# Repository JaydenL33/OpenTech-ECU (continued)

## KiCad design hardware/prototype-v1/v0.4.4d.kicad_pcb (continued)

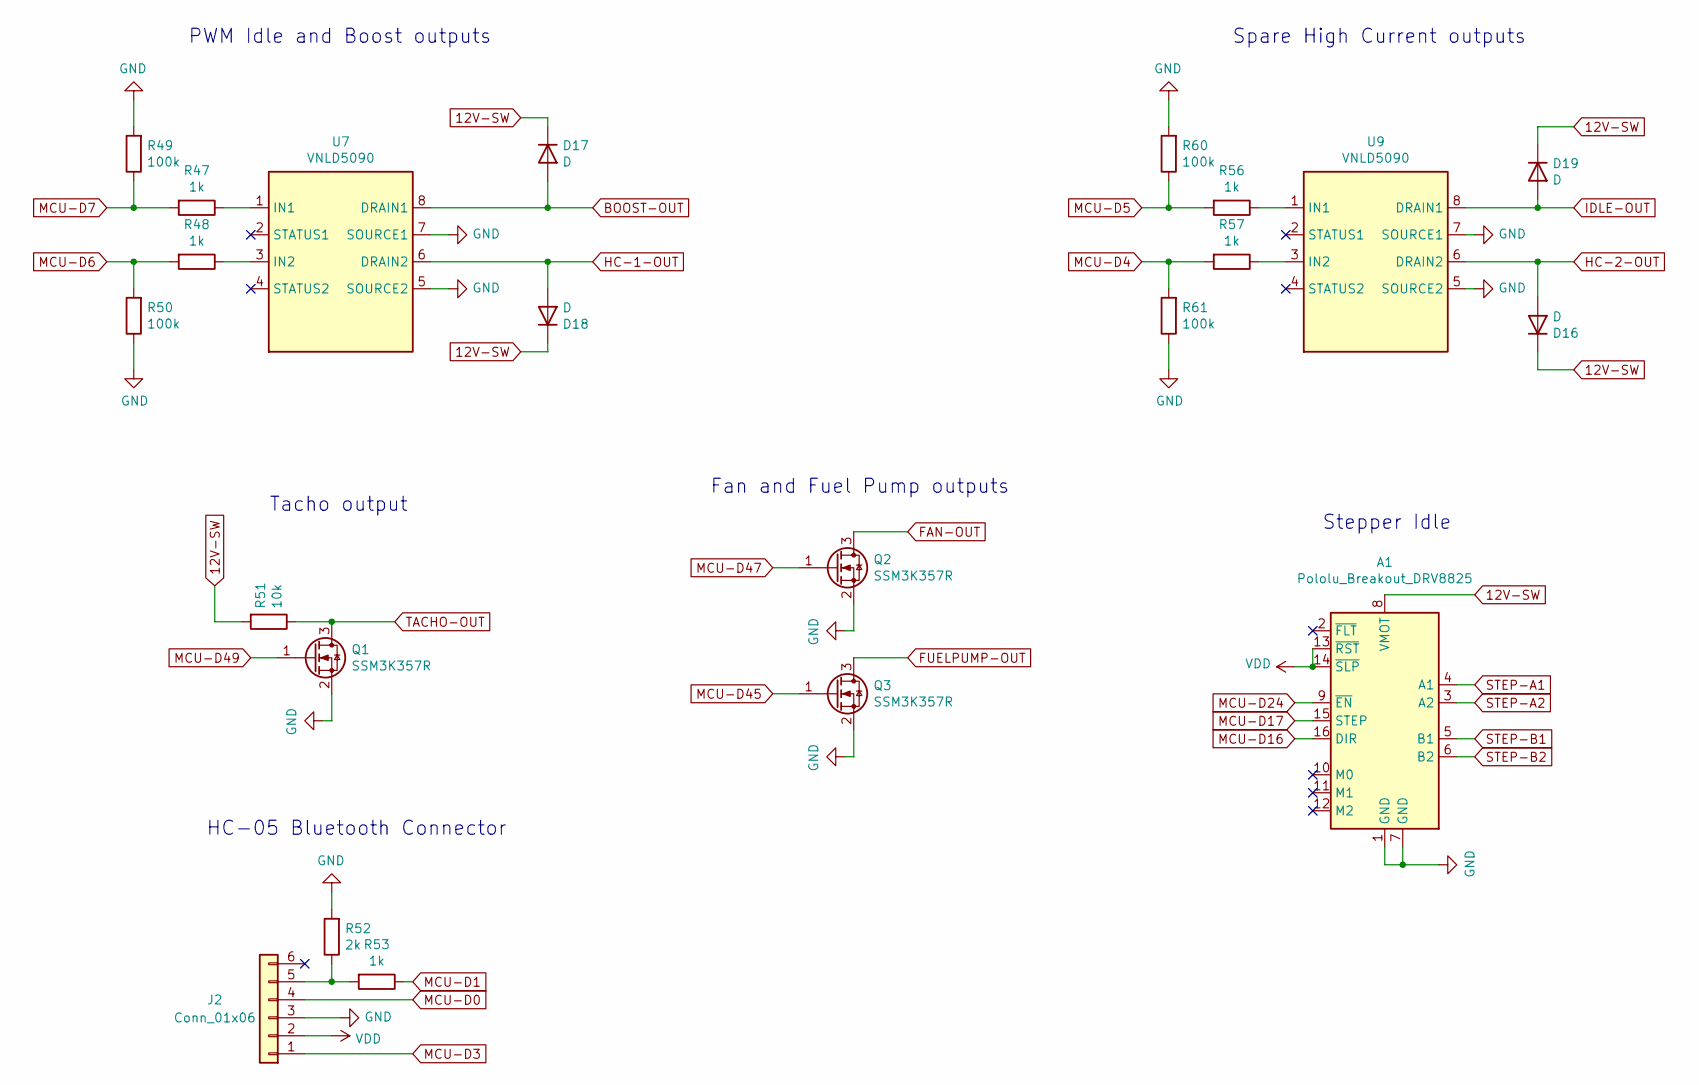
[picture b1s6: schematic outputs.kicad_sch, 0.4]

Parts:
A1: Pololu_Breakout_DRV8825; Pololu_Breakout-16_15.2x20.3mm
D16, D17, D18, D19: D; D_SOD-123F; Manufacturer_Part_Number S110FA; Digikey Part Number S110FACT-ND
J2: Conn_01x06; PinHeader_1x06_P2.54mm_Vertical
Q1, Q2, Q3: SSM3K357R; SOT-23; Manufacturer_Part_Number SSM3K357R; Digikey Part Number SSM3K357RLFCT-ND
R47, R48, R53, R56, R57: 1k; R_0805_2012Metric; Manufacturer_Part_Number RC0805FR-071KL; Digikey Part Number 311-1.00KCRCT-ND
R49, R50, R60, R61: 100k; R_0805_2012Metric; Manufacturer_Part_Number RC0805FR-07100KL; Digikey Part Number 311-100KCRCT-ND
R51: 10k; R_0805_2012Metric; Manufacturer_Part_Number RC0805JR-0710KL; Digikey Part Number 311-10KARCT-ND
R52: 2k; R_0805_2012Metric; Manufacturer_Part_Number RC0805FR-072KL; Digikey Part Number 311-2.00KCRCT-ND
U7, U9: VNLD5090; SOIC-8_3.9x4.9mm_P1.27mm; Manufacturer_Part_Number VNLD5090-E; Digikey Part Number 497-18682-ND

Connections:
12V-SW: A1.8 (VMOT), D16.1 (K), D17.1 (K), D18.1 (K), D19.1 (K), R51.2; also elsewhere on the board
BOOST-OUT: D17.2 (A), U7.8 (DRAIN1); also elsewhere on the board
FAN-OUT: Q2.3 (D); also elsewhere on the board
FUELPUMP-OUT: Q3.3 (D); also elsewhere on the board
GND: A1.1 (GND), A1.7 (GND), J2.3, Q1.2 (S), Q2.2 (S), Q3.2 (S), R49.2, R50.1, R52.2, R60.2, R61.1, U7.5 (SOURCE2), U7.7 (SOURCE1), U9.5 (SOURCE2), U9.7 (SOURCE1); also elsewhere on the board
HC-1-OUT: D18.2 (A), U7.6 (DRAIN2); also elsewhere on the board
HC-2-OUT: D16.2 (A), U9.6 (DRAIN2); also elsewhere on the board
IDLE-OUT: D19.2 (A), U9.8 (DRAIN1); also elsewhere on the board
MCU-D0: J2.4; also elsewhere on the board
MCU-D1: R53.1; also elsewhere on the board
MCU-D3: J2.1; also elsewhere on the board
MCU-D4: R57.2, R61.2; also elsewhere on the board
MCU-D5: R56.2, R60.1; also elsewhere on the board
MCU-D6: R48.2, R50.2; also elsewhere on the board
MCU-D7: R47.2, R49.1; also elsewhere on the board
MCU-D16: A1.16 (DIR); also elsewhere on the board
MCU-D17: A1.15 (STEP); also elsewhere on the board
MCU-D24: A1.9 (~EN); also elsewhere on the board
MCU-D45: Q3.1 (G); also elsewhere on the board
MCU-D47: Q2.1 (G); also elsewhere on the board
MCU-D49: Q1.1 (G); also elsewhere on the board
unnamed: J2.5, R52.1, R53.2
unnamed: R47.1, U7.1 (IN1)
unnamed: R48.1, U7.3 (IN2)
unnamed: R56.1, U9.1 (IN1)
unnamed: R57.1, U9.3 (IN2)
STEP-A1: A1.4 (A1); also elsewhere on the board
STEP-A2: A1.3 (A2); also elsewhere on the board
STEP-B1: A1.5 (B1); also elsewhere on the board
STEP-B2: A1.6 (B2); also elsewhere on the board
TACHO-OUT: Q1.3 (D), R51.1; also elsewhere on the board
VDD: A1.13 (~RST), A1.14 (~SLP), J2.2; also elsewhere on the board

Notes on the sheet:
PWM Idle and Boost outputs
Spare High Current outputs
Stepper Idle
HC-05 Bluetooth Connector
Fan and Fuel Pump outputs
Tacho output

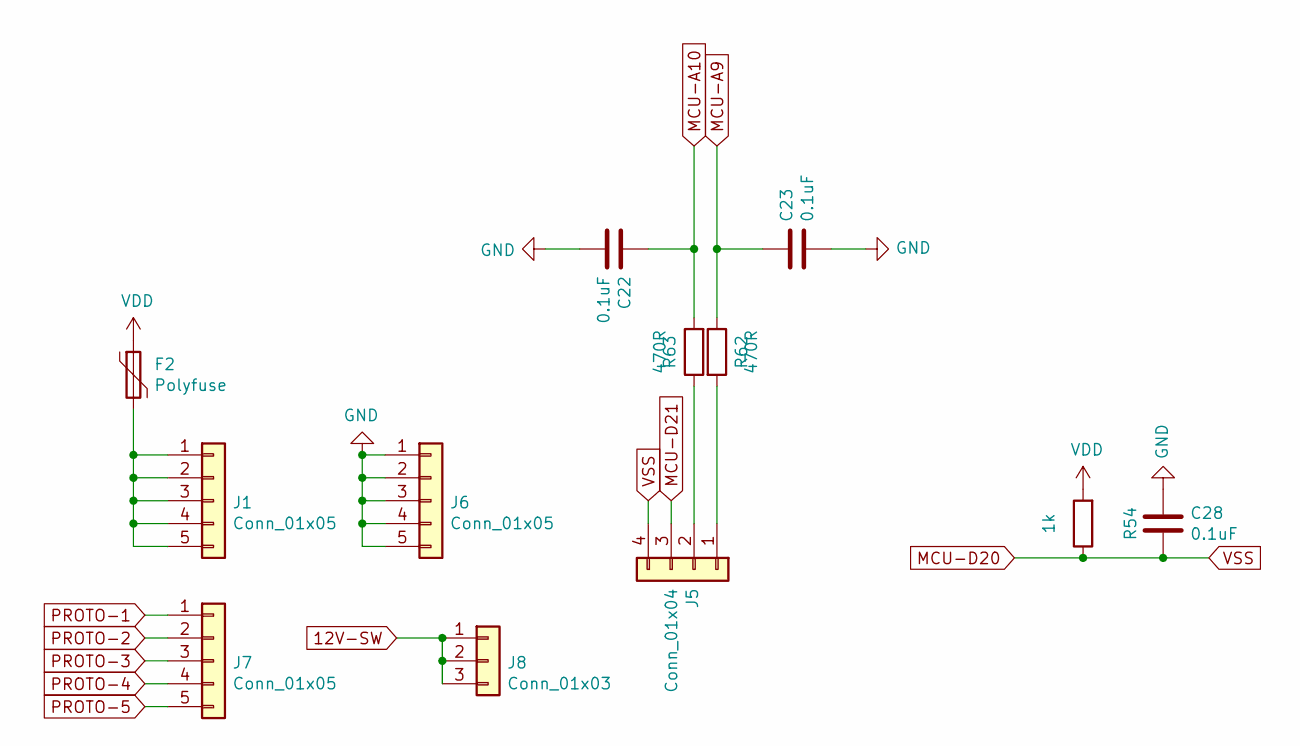
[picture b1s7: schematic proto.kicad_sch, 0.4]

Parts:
C22, C23, C28: 0.1uF; C_0805_2012Metric; Manufacturer_Part_Number CC0805KRX7R9BB104; Digikey Part Number 311-1140-1-ND
F2: Polyfuse; Fuse_1812_4532Metric; Manufacturer_Part_Number 0ZCC0050FF2C; Digikey Part Number 507-1361-1-ND
J1, J6, J7: Conn_01x05; PinHeader_1x05_P2.54mm_Vertical
J5: Conn_01x04; PinHeader_1x04_P2.54mm_Vertical
J8: Conn_01x03; PinHeader_1x03_P2.54mm_Vertical
R54: 1k; R_0805_2012Metric; Manufacturer_Part_Number RC0805FR-071KL; Digikey Part Number 311-1.00KCRCT-ND
R62, R63: 470R; R_0805_2012Metric; Manufacturer_Part_Number ERJ-6ENF4700V; Digikey Part Number P470CCT-ND

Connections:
12V-SW: J8.1, J8.2, J8.3; also elsewhere on the board
GND: C22.2, C23.2, C28.1, J6.1, J6.2, J6.3, J6.4, J6.5; also elsewhere on the board
MCU-A9: C23.1, R63.1; also elsewhere on the board
MCU-A10: C22.1, R62.2; also elsewhere on the board
MCU-D20: C28.2, J5.4, R54.1; also elsewhere on the board
MCU-D21: J5.3; also elsewhere on the board
unnamed: F2.2, J1.1, J1.2, J1.3, J1.4, J1.5
unnamed: J5.1, R63.2
unnamed: J5.2, R62.1
PROTO-1: J7.1; also elsewhere on the board
PROTO-2: J7.2; also elsewhere on the board
PROTO-3: J7.3; also elsewhere on the board
PROTO-4: J7.4; also elsewhere on the board
PROTO-5: J7.5; also elsewhere on the board
VDD: F2.1, R54.2; also elsewhere on the board

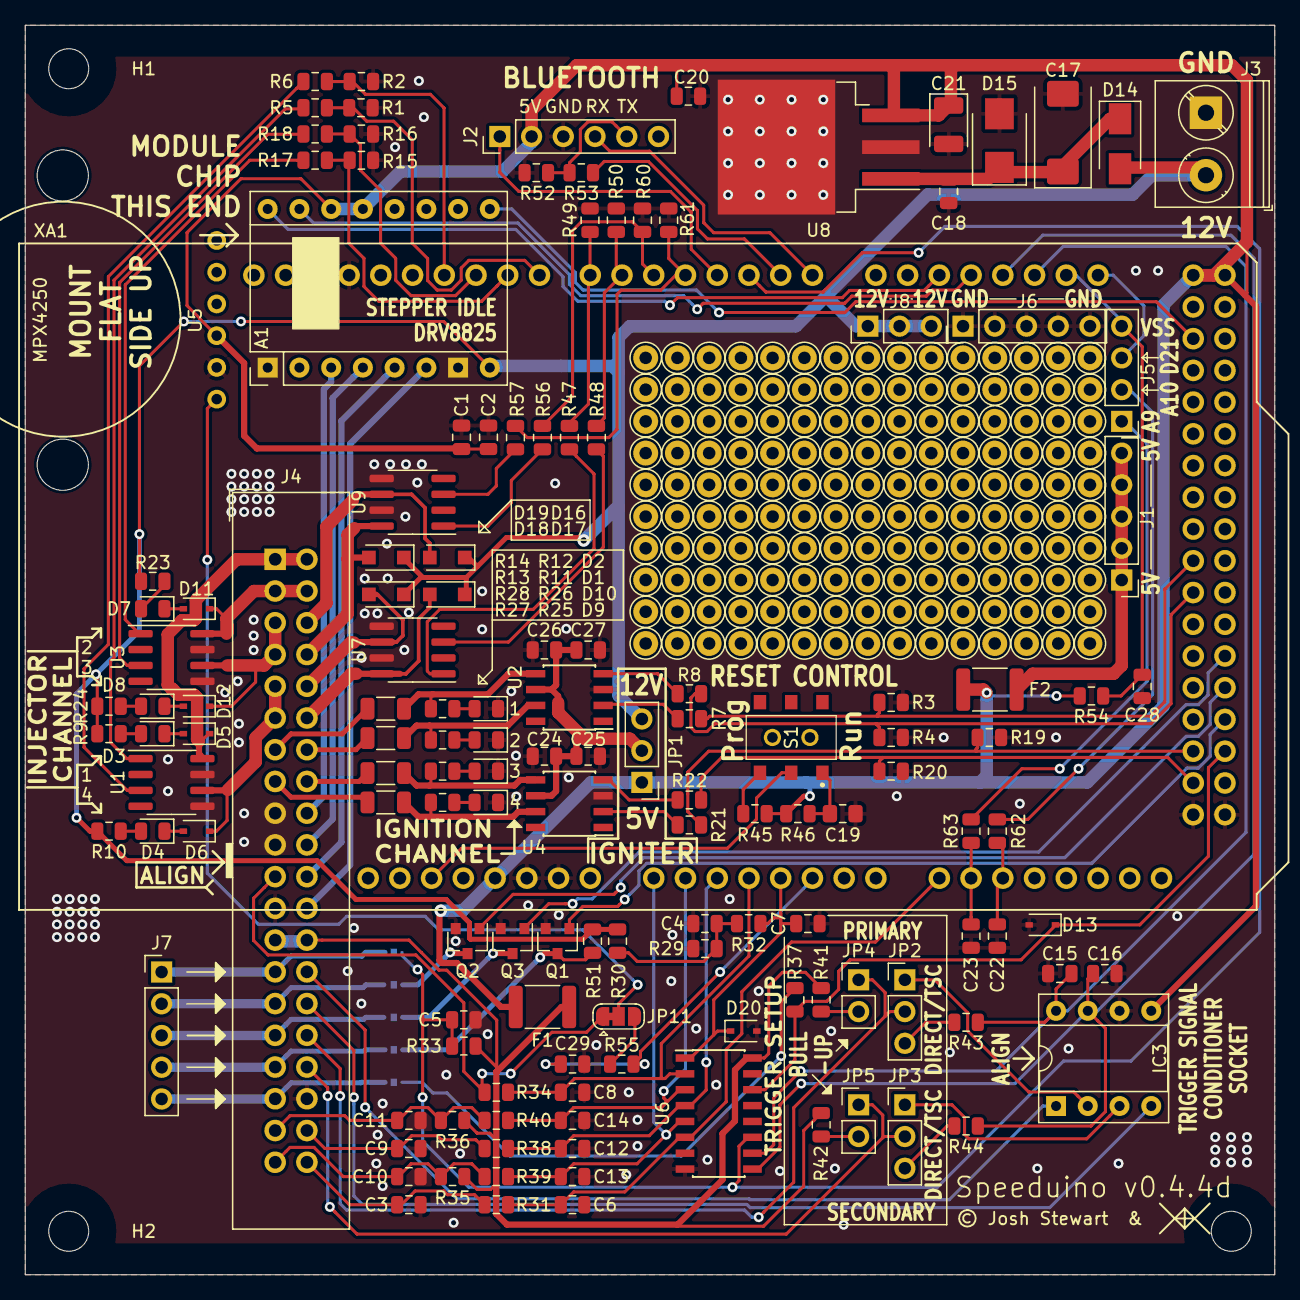
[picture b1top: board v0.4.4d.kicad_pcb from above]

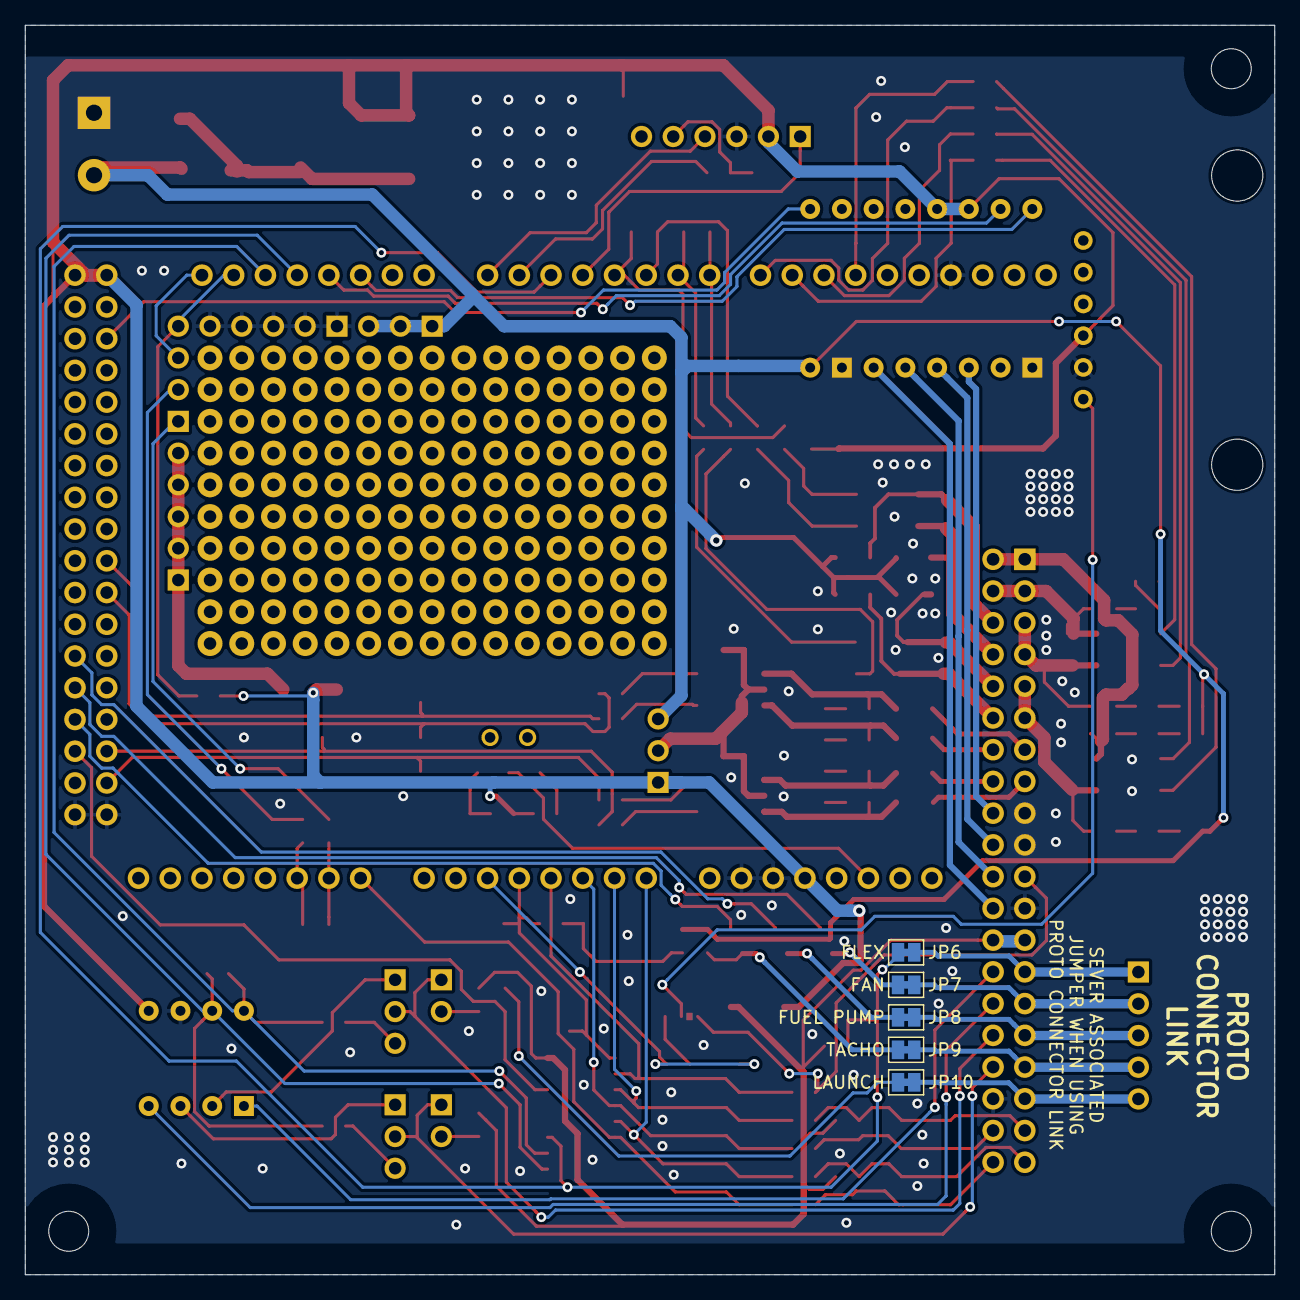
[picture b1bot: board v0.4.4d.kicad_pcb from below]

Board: 2 copper layers, 100.0 x 100.0 mm, 150 parts (5 on the bottom side), 120 nets.

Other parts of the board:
H1, H2, H3: MountingHole_3.2mm_M3

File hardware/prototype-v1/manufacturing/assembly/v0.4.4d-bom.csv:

"Refs","Value","Footprint","Qty","DNP","Manufacturer","MPN"
"A1","Pololu_Breakout_DRV8825","Module:Pololu_Breakout-16_15.2x20.3mm","1","","",""
"C1,C15","0.01uF","Capacitor_SMD:C_0805_2012Metric","2","","Yageo","CC0805KRX7R9BB103"
"C2,C25,C27","1uF","Capacitor_SMD:C_0805_2012Metric","3","","Yageo","CC0805KKX7R7BB105"
"C3,C4,C9-C11,C16,C18,C20,C22-C24,C26,C28","0.1uF","Capacitor_SMD:C_0805_2012Metric","13","","Yageo","CC0805KRX7R9BB104"
"C5-C7,C12-C14","0.22uF","Capacitor_SMD:C_0805_2012Metric","6","","Samsung","CL21B224KOCNNNC"
"C8,C29","470pf","Capacitor_SMD:C_0805_2012Metric","2","","Yageo","CC0805KRX7R9BB471"
"C17","10uF","Capacitor_Tantalum_SMD:CP_EIA-7343-31_Kemet-D","1","","Kemet","T491D106K050AT"
"C19","22uF","Speeduino_Legacy:C_0805_2012Metric_Pad1.15x1.40mm_HandSolder","1","","Samsung","CL21A226KQCLRNC"
"C21","47uF","Capacitor_Tantalum_SMD:CP_EIA-3528-21_Kemet-B","1","","AVX","TAJB476K006RNJ"
"D1-D4,D7-D10","LED","LED_SMD:LED_0805_2012Metric","8","","Osram","LH R974-LP-1"
"D5,D6,D11,D12","D","Diode_SMD:D_SOD-323","4","","MCC","1N4448WX-TP"
"D13,D20","D_Zener","Diode_SMD:D_SOD-323","2","","On Semi","MM3Z5V1ST1G"
"D14","B130-13-F","Diode_SMD:D_SMA","1","","Diodes Inc","B130-13-F"
"D15","D_TVS","Diode_SMD:D_SMB","1","","Bournes Inc.","SMBJ40A-Q"
"D16-D19","D","Diode_SMD:D_SOD-123F","4","","ONSEMI","S110FA"
"F1,F2","Polyfuse","Fuse:Fuse_1812_4532Metric","2","","Bel Fuse","0ZCC0050FF2C"
"IC3","Trig Cond Socket","Package_DIP:DIP-8_W7.62mm_Socket","1","","",""
"J1,J6,J7","Conn_01x05","Connector_PinHeader_2.54mm:PinHeader_1x05_P2.54mm_Vertical","3","","",""
"J2","Conn_01x06","Connector_PinHeader_2.54mm:PinHeader_1x06_P2.54mm_Vertical","1","","",""
"J3","Conn_01x02","TerminalBlock_Phoenix:TerminalBlock_Phoenix_PT-1,5-2-5.0-H_1x02_P5.00mm_Horizontal","1","","",""
"J4","Conn_02x20_Counter_Clockwise","Connector_IDC:IDC-Header_2x20_P2.54mm_Vertical","1","","",""
"J5","Conn_01x04","Connector_PinHeader_2.54mm:PinHeader_1x04_P2.54mm_Vertical","1","","",""
"J8","Conn_01x03","Connector_PinHeader_2.54mm:PinHeader_1x03_P2.54mm_Vertical","1","","",""
"JP1","Ignition Voltage","Connector_PinHeader_2.54mm:PinHeader_1x03_P2.54mm_Vertical","1","","Harwin Inc","M20-9990345"
"JP2,JP3","VR-HALL","Connector_PinHeader_2.54mm:PinHeader_1x03_P2.54mm_Vertical","2","","Harwin Inc","M20-9990345"
"JP4,JP5","PULL-UP","Connector_PinHeader_2.54mm:PinHeader_1x02_P2.54mm_Vertical","2","","Harwin Inc","M20-9990245 "
"JP6-JP10","SolderJumper_2_Bridged","Jumper:SolderJumper-2_P1.3mm_Bridged_Pad1.0x1.5mm","5","","",""
"JP11","Jumper_3_Bridged12","Jumper:SolderJumper-3_P1.3mm_Bridged12_RoundedPad1.0x1.5mm","1","","",""
"Q1-Q3","SSM3K357R","Package_TO_SOT_SMD:SOT-23","3","","Toshiba","SSM3K357R"
"R1-R4,R15,R16,R19,R20,R49,R50,R60,R61","100k","Resistor_SMD:R_0805_2012Metric","12","","Yageo","RC0805FR-07100KL"
"R5-R8,R17,R18,R21,R22,R29,R37,R41,R42,R47,R48,R53,R54,R56,R57","1k","Resistor_SMD:R_0805_2012Metric","18","","Yageo","RC0805FR-071KL"
"R9-R12,R23-R26,R33","2.4k","Resistor_SMD:R_0805_2012Metric","9","","Yageo","RC0805FR-072K4L"
"R13,R14,R27,R28","10R","Resistor_SMD:R_1206_3216Metric","4","","Yageo","RC1206FR-0710RL"
"R30","3.9k","Resistor_SMD:R_0805_2012Metric","1","","Yageo","RC0805FR-073K9L"
"R31,R32,R34,R38-R40,R55,R62,R63","470R","Resistor_SMD:R_0805_2012Metric","9","","Panasonic","ERJ-6ENF4700V"
"R35,R36","2.49k","Resistor_SMD:R_0805_2012Metric","2","","Yageo","RT0805BRD072K49L"
"R43,R44","220R","Resistor_SMD:R_0805_2012Metric","2","","Yageo","RC0805FR-07220RL"
"R45,R51","10k","Resistor_SMD:R_0805_2012Metric","2","","Yageo","RC0805JR-0710KL"
"R46","120R","Resistor_SMD:R_0805_2012Metric","1","","Yageo","RC0805FR-07120RL"
"R52","2k","Resistor_SMD:R_0805_2012Metric","1","","Yageo","RC0805FR-072KL"
"S1","AYZ0202AGRLC","Misc:AYZ0202AGRLC","1","","C & K COMPONENTS","AYZ0202AGRLC"
"U1,U3,U7,U9","VNLD5090","Package_SO:SOIC-8_3.9x4.9mm_P1.27mm","4","","STMicro","VNLD5090-E"
"U2,U4","IXDN602","Package_SO:SOIC-8_3.9x4.9mm_P1.27mm","2","","IXYS","IXDN602SIATR"
"U5","MPX4250","Misc:MPX4250","1","","NXP","MPX4250AP"
"U6","SP720","Package_SO:SOIC-16_3.9x9.9mm_P1.27mm","1","","Littelfuse","SP720ABTG"
"U8","LM2940S-5.0/NOPB","Package_TO_SOT_SMD:TO-263-3_TabPin2","1","","TI","LM2940S-5.0/NOPB"
"XA1","Arduino_Mega2560_Shield","Shields:Arduino_Mega2560_Shield_IO_Only","1","","",""

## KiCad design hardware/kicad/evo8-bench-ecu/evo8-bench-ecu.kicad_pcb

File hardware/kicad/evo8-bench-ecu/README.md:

# Evo VIII bench-prototype ECU — unreviewed KiCad schematic + PCB draft

> **SUPERSEDED — DO NOT USE FOR THE PROTOTYPE.** The selected bench design is
> `hardware/prototype-v1/v0.4.4d.kicad_pro` (Speeduino v0.4.4d SMD). This older
> custom STM32 board is retained as an exploratory draft only. If KiCad shows
> “UNROUTED” or “OpenTech-ECU REV A”, you are in this folder, not prototype-v1.
>
> **STATUS: UNREVIEWED BENCH SCHEMATIC + UNROUTED PCB DRAFT. NOT MANUFACTURABLE.
> NOT AUTOMOTIVE-QUALIFIED. NOT AN EVO VIII PLUG-IN. DO NOT FABRICATE OR CONNECT TO A VEHICLE.**

This package was produced in a time-boxed independent Codex hardware pass and
then imported into the repository for review. It has **not** been designed or
signed off by a qualified automotive electronics engineer. Treat every
component value, pin, net and protection choice as a hypothesis to be reviewed.

## What exists

| Artefact | Present? | Notes |
|---|---|---|
| KiCad 9 project + hierarchical schematic | Yes | Seven sheets, 305 BOM lines/components |
| Netlist (KiCad XML) | Yes | 198 nets |
| BOM | Yes | Real manufacturer part numbers; sourcing/derating not reviewed |
| Pin map | Yes | Bench connector names, **not** OEM Evo cavities |
| Test point list | Yes | Scope points for rails, MCU, injectors, triggers, CAN |
| ERC report | Yes | 0 violations reported by the generator's KiCad CLI |
| Schematic SVG | Yes | `reports/schematic-svg/` |
| PCB layout draft | Yes, **NOT USABLE** | `.kicad_pcb` with 305 footprints; 37 tracks/vias, 499 unconnected items, 14 DRC violations. Unrouted placement draft, not a manufacturable board |
| Manufacturing outputs | **No** | No gerbers, drill, assembly or fabrication drawing |
| Thermal/EMC/transient validation | **No** | Not started |
| Evo connector/pinout | **No** | OEM harness remains UNVERIFIED |
| Independent review | **No** | Required before any build |

ERC passing means the captured schematic has no KiCad electrical-rule
violations under the chosen settings. It does **not** prove the circuit is safe,
correct, manufacturable, automotive-qualified or compatible with an Evo VIII.

## Intended architecture (as captured)

- **Power:** fused 12 V bench input, reverse-polarity MOSFET, TVS, e-fuse
  (TPS259260), 5 V/3.3 V rails, reset supervisor, bench ARM pushbutton and
  hardware-inhibit path. No load-dump/automotive qualification.
- **MCU:** STM32H743VIT6, external HSE, SWD, USB, CAN transceiver, watchdog.
- **Injectors:** four low-side bench sinks (IRLZ44N TO-220) with flyback,
  clamp, 0.22 Ω shunts and test points. **No peak/hold current control, no
  injector characterisation and no vehicle injector approval.**
- **Ignition:** four logic-level outputs intended for **external, verified
  igniters**; no direct coil drive and no high-voltage section.
- **Triggers:** two simulated crank/cam inputs with comparator conditioning and
  scope points. These are not proof of the 4G63 trigger pattern.
- **Sensors:** four protected analogue channels (not a complete Evo sensor set).
- **Auxiliary:** four low-side outputs and one relay driver, bench loads only.
- **Connectors:** Phoenix-style bench terminal blocks and headers. Pin numbers
  are **not** Mitsubishi OEM cavity numbers.

## Review blockers before fabrication

1. Complete the PCB routing and fix all DRC violations; review every clearance,
   creepage, current path and thermal pad. The current draft has 499 unconnected
   items and 14 DRC violations.
2. Review the power input for reverse polarity, load dump, transient energy,
   fuse coordination, inrush and brownout.
3. Verify the TPS259260 configuration, e-fuse current limit, SOA and thermal
   design for the intended dummy loads.
4. Review injector sink SOA, flyback energy, shunt power, gate drive and
   default-off behaviour. No real injector until the driver is proven.
5. Review the ignition logic-level interface against a **verified** igniter
   input; do not assume TTL/CMOS thresholds or polarity.
6. Review CAN transceiver protection, termination, ground offsets and EMC.
7. Verify STM32H743 pin assignments against the exact package datasheet and
   alternate-function table. The pin map is not independently checked.
8. Verify all BOM parts are active, sourceable, correctly rated and derated.
9. Add a hardware watchdog and output-interlock circuit review; the firmware
   skeleton's interlock is software, not an independent safety barrier.
10. Run the unpowered and powered bench plan in
    [`AUDIT/EVO8_BENCH_TEST_PLAN.md`](../../../../AUDIT/EVO8_BENCH_TEST_PLAN.md)
    with current-limited supplies and dummy loads.

## Licence

The original hardware design files in this directory are intended to be
distributed under **CERN-OHL-S-2.0** (see `LICENSE-CERN-OHL-S-2.0.txt`). They are
not derived from the Speeduino Hardware repository. Review the licence and
provenance before manufacture or redistribution.

## Reproduction and evidence

The files were generated with a local KiCad 9 installation fetched into an
isolated workspace. The generator script is retained under `tools/` for review,
but it depends on local KiCad libraries and is not a manufacturing build system.
The ERC JSON is in `reports/erc.json`. A DRC run on the unrouted placement draft
is in `reports/drc.json`: **14 violations (13 dangling vias + 1 clearance) and 499 unconnected items**. It is not
a routable/manufacturable board and must not be fabricated.

Do not claim Gate 1 or Gate 2 from this package. See
`AUDIT/HARDWARE_STATUS.md`, `AUDIT/ELECTRICAL_DESIGN_REVIEW.md` and
`AUDIT/RELEASE_GATES.md`.

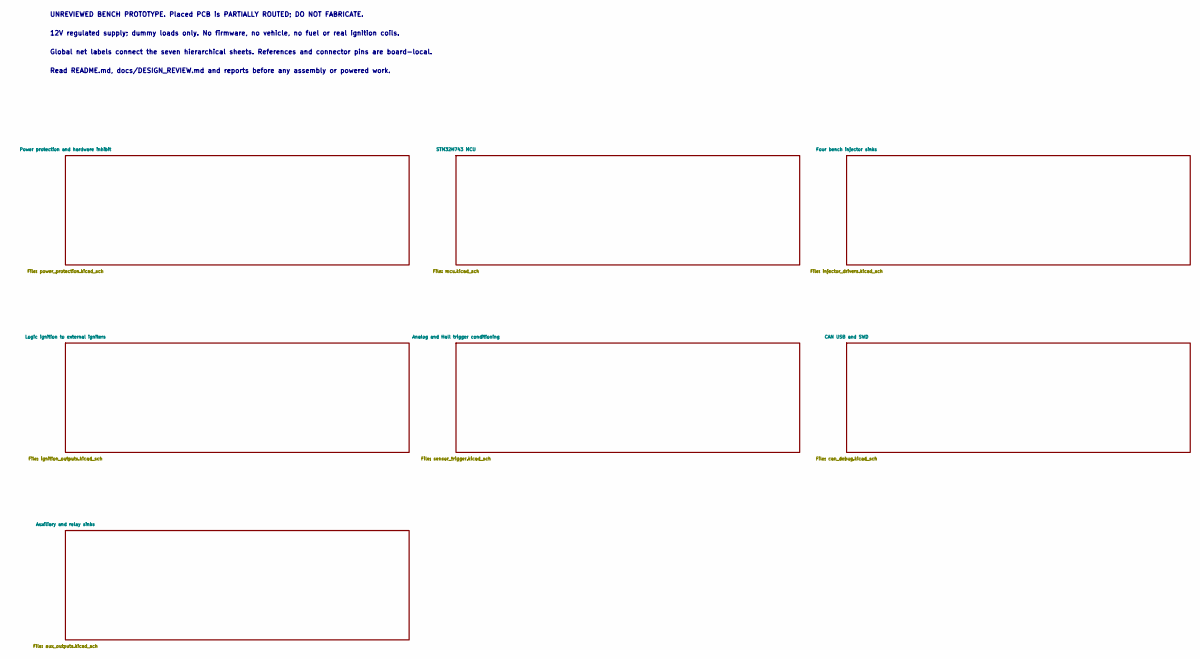
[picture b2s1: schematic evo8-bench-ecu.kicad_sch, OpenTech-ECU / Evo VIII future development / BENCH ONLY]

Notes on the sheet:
UNREVIEWED BENCH PROTOTYPE. Placed PCB is PARTIALLY ROUTED; DO NOT FABRICATE.
12V regulated supply; dummy loads only. No firmware, no vehicle, no fuel or real ignition coils.
Global net labels connect the seven hierarchical sheets. References and connector pins are board-local.
Read README.md, docs/DESIGN_REVIEW.md and reports before any assembly or powered work.

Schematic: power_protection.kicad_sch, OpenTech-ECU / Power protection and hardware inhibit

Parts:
C100, C105, C108, C110, C111, C112, C113: 100n; C_0805_2012Metric; MPN GRM21BR71H104KA01L
C101: 1n; C_0805_2012Metric; MPN GRM21B5C1H102JA01L
C102, C109: 1u; C_0805_2012Metric; MPN GRM21BR71H105KA12L
C103: 220u 35V; CP_Radial_D8.0mm_P3.50mm; MPN UHE1V221MPD
C104: 330u 25V; CP_Radial_D8.0mm_P3.50mm; MPN UHE1E331MPD
C106, C107: 10u; C_0805_2012Metric; MPN GRM21BR61A106KE19L
D100, D103: BZT52C12; D_SOD-123; MPN BZT52C12-7-F
D101: SMBJ12A; D_SMB; MPN SMBJ12A
D102: SS34; D_SMA; MPN SS34
D104: BAT54WS; D_SOD-323; MPN BAT54WS-7-F
F100: 2A; Fuse_1206_3216Metric; MPN 0467002.NR
J100: J_PWR 12V BENCH ONLY; TerminalBlock_Phoenix_MKDS-1,5-2-5.08_1x02_P5.08mm_Horizont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; MPN 1715721
J101: J_ESTOP EXTERNAL NC CONTACTS; TerminalBlock_Phoenix_MKDS-1,5-4-5.08_1x04_P5.08mm_Horizont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; MPN 1715747
L100: 33uH; L_Bourns_SRR1260; MPN SRR1260-330M
Q100, Q101: IRF4905PBF; TO-220-3_Vertical; MPN IRF4905PBF
Q102: MMBT3904LT1G; SOT-23; MPN MMBT3904LT1G
R100, R107, R108, R111, R114, R116, R117, R118: 100k; R_0805_2012Metric; MPN RC0805FR-07100KL
R101: 45.3k; R_0805_2012Metric; MPN RC0805FR-0745K3L
R102: 47k; R_0805_2012Metric; MPN RC0805FR-0747KL
R103, R109, R113, R115: 10k; R_0805_2012Metric; MPN RC0805FR-0710KL
R104: 0; R_2512_6332Metric; MPN RC2512JK-070RL
R105: 0; R_0805_2012Metric; MPN RC0805FR-070RL
R106, R112: 1k; R_0805_2012Metric; MPN RC0805FR-071KL
R110: 4.7k; R_0805_2012Metric; MPN RC0805FR-074K7L
SW100: ARM BENCH; SW_PUSH_6mm; MPN B3F-1000
TP100: VIN_BENCH; TestPoint_THTPad_D2.0mm_Drill1.0mm; MPN 5010
TP101: +12V_PROTECTED; TestPoint_THTPad_D2.0mm_Drill1.0mm; MPN 5010
TP102: +12V_ACT; TestPoint_THTPad_D2.0mm_Drill1.0mm; MPN 5010
TP103: +5V; TestPoint_THTPad_D2.0mm_Drill1.0mm; MPN 5010
TP104: +3V3; TestPoint_THTPad_D2.0mm_Drill1.0mm; MPN 5010
TP105: NRST; TestPoint_THTPad_D2.0mm_Drill1.0mm; MPN 5010
TP106: ARMED; TestPoint_THTPad_D2.0mm_Drill1.0mm; MPN 5010
TP107: ACT_EN; TestPoint_THTPad_D2.0mm_Drill1.0mm; MPN 5010
TP108: PGND; TestPoint_THTPad_D2.0mm_Drill1.0mm; MPN 5010
TP109: GND; TestPoint_THTPad_D2.0mm_Drill1.0mm; MPN 5010
TP110: ESTOP_OK; TestPoint_THTPad_D2.0mm_Drill1.0mm; MPN 5010
U100: TPS259260DRCR; VSON-10-1EP_3x3mm_P0.5mm_EP1.65x2.4mm_ThermalVias; MPN TPS259260DRCR
U101: LM2596S-5.0/NOPB; TO-263-5_TabPin3; MPN LM2596S-5.0/NOPB
U102: LD1117S33TR; SOT-223-3_TabPin2; MPN LD1117S33TR
U103: TPS3808G33DBVR; SOT-23-6; MPN TPS3808G33DBVR
U104: TPS3430WDRCR; VSON-10-1EP_3x3mm_P0.5mm_EP1.65x2.4mm; MPN TPS3430WDRCR
U105: SN74HC08DR; SOIC-14_3.9x8.7mm_P1.27mm; MPN SN74HC08DR
U106: SN74HC74DR; SOIC-14_3.9x8.7mm_P1.27mm; MPN SN74HC74DR

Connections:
+3V3: C107.1, C108.1, C110.1, C111.1, C112.1, C113.1, R106.1, R113.2, R115.2, SW100.1, TP104.1, U102.2 (VO), U103.3 (~MR), U103.5 (SENSE), U103.6 (VDD), U104.1 (VDD1), U104.10 (VDD2), U105.14 (VCC), U106.2 (D), U106.4 (~S), U106.10 (~S), U106.14 (VCC); also elsewhere on the board
+5V: C104.1, C105.1, C106.1, L100.2, TP103.1, U101.4 (FB), U102.3 (VI); also elsewhere on the board
+12V_ACT: C109.1, Q101.2 (D), R112.1, TP102.1; also elsewhere on the board
+12V_PROTECTED: C102.1, C103.1, J101.1, TP101.1, U100.6 (OUT), U100.7 (OUT), U100.8 (OUT), U101.1 (VIN)
ACT_EN: R110.1, R118.1, TP107.1, U105.8; also elsewhere on the board
ACT_FEED: D103.1 (K), J101.2, Q101.3 (S), R108.2
ACT_PWR_BASE: Q102.1 (B), R110.2, R111.1
ACT_PWR_COLLECTOR: Q102.3 (C), R109.2
ACT_PWR_GATE: D103.2 (A), Q101.1 (G), R108.1, R109.1
AGND: R105.1; also elsewhere on the board
ARMED: TP106.1, U105.4, U106.5 (Q); also elsewhere on the board
ARM_CLEAR_N: U105.3, U105.10, U106.1 (~R)
ARM_CLOCK: R116.1, SW100.2, U106.3 (C)
BROWN_RESET_N: D104.1 (K), R113.1, U103.1 (~RESET)
BUCK_SW: D102.1 (K), L100.1, U101.2 (OUT)
EFUSE_ILIM: R101.1, U100.10 (ILIM)
EFUSE_SLEW: C101.1, U100.1 (dV/dT)
EFUSE_UVLO: R102.2, R103.1, U100.2 (EN/UVLO)
ENABLE_REQ: U105.6, U105.9
ESTOP_OK: J101.4, R107.1, TP110.1, U105.2; also elsewhere on the board
ESTOP_SEND: J101.3, R106.2
GND: C105.2, C106.2, C107.2, C108.2, C110.2, C111.2, C112.2, C113.2, R104.1, R105.2, R107.2, R114.2, R116.2, R117.2, R118.2, TP109.1, U102.1 (GND), U103.2 (GND), U104.3 (SET0), U104.5 (GND), U104.6 (SET1), U104.11 (GND), U105.7 (GND), U105.12, U105.13, U106.7 (GND), U106.11 (C), U106.12 (D), U106.13 (~R); also elsewhere on the board
MCU_ENABLE: R117.1, U105.5; also elsewhere on the board
NRST: D104.2 (A), R115.1, TP105.1, U104.8 (~WDO), U105.1; also elsewhere on the board
PGND: C100.2, C101.2, C102.2, C103.2, C104.2, C109.2, D101.2 (A), D102.2 (A), J100.2, Q102.2 (E), R100.2, R101.2, R103.2, R104.2, R111.2, R112.2, TP108.1, U100.11 (GND), U101.3 (GND), U101.5 (~ON/OFF); also elsewhere on the board
REV_GATE: D100.2 (A), Q100.1 (G), R100.1
VIN_BENCH: F100.1, J100.1, TP100.1
VIN_FUSED: F100.2, Q100.2 (D)
VIN_REVERSE_OK: C100.1, D100.1 (K), D101.1 (K), Q100.3 (S), R102.1, U100.3 (VIN), U100.4 (VIN), U100.5 (VIN)
WD_KICK: R114.1, U104.7 (WDI); also elsewhere on the board

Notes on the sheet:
10.0-12.6V regulated bench source ONLY. Set external current limit before applying power.
J_ESTOP pins1-2: external NC power contact; pins3-4: independent NC logic contact. No jumpers fitted.
ACT_EN = ARMED AND MCU_ENABLE AND NRST AND ESTOP_OK. Reset/E-stop clears arm latch.
TPS3430: falling edges every35ms; guaranteed service interval25.9-46.8ms; reset170-230ms.
PWR_FLAG marks intended source nets for ERC; it does not verify voltage, current, or safe operation.
